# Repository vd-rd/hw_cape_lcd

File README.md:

# hw_cape_lcd
LCD module for embedded projects

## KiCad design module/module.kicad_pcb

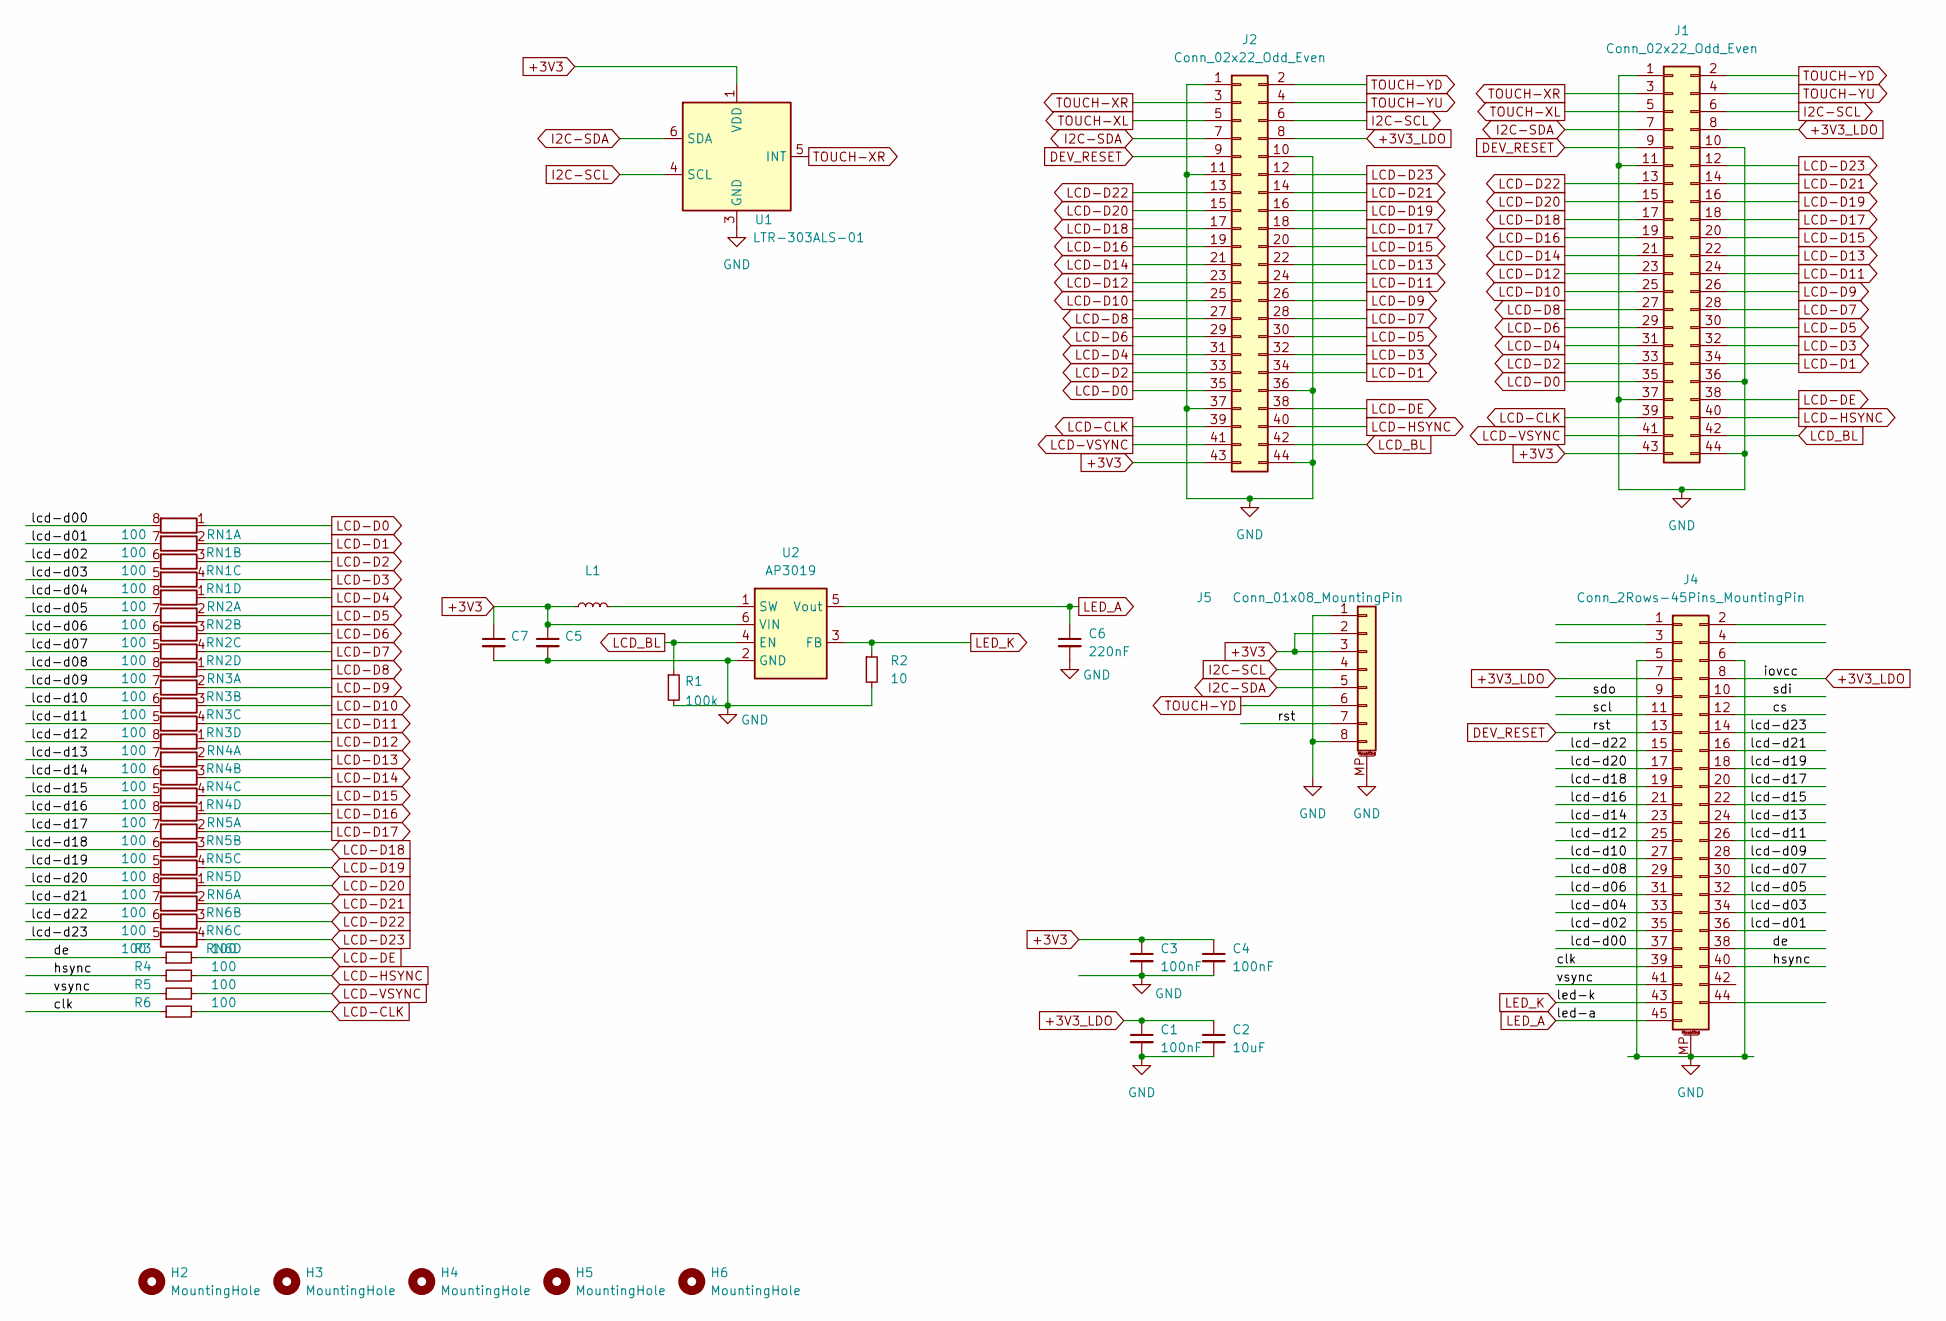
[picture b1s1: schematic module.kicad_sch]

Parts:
C1, C3, C4: 100nF; C_0402_1005Metric
C2: 10uF; C_0603_1608Metric
C5, C7: (no value)
C6: 220nF; C_0603_1608Metric
H2, H3, H4, H5, H6: MountingHole; MountingHole_2.7mm_M2.5_DIN965
J1, J2: Conn_02x22_Odd_Even; PinHeader_2x22_P1.27mm_Vertical_SMD
J4: Conn_2Rows-45Pins_MountingPin; Hirose_FH12-45S-0.5SH_1x45-1MP_P0.50mm_Horizontal
J5: Conn_01x08_MountingPin; Hirose_FH12-8S-0.5SH_1x08-1MP_P0.50mm_Horizontal
L1: (no value)
R1: 100k; R_0402_1005Metric
R2: 10; R_0805_2012Metric
R3, R4, R5, R6: 100; R_0603_1608Metric
RN1, RN2, RN3, RN4, RN5, RN6: 100; R_Array_Convex_4x0603
U1: LTR-303ALS-01; Lite-On_LTR-303ALS-01
U2: AP3019; SOT-23-6

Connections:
+3V3: C3.1, C4.1, C5.1, C7.1, J1.43, J2.43, J5.2, J5.3, L1.1, U1.1 (VDD), U2.6 (VIN)
+3V3_LDO: C1.1, C2.1, J1.8, J2.8, J4.7, J4.8
/clk: J4.39, R6.1
/cs: J4.12
/de: J4.38, R3.1
/hsync: J4.40, R4.1
/lcd-d00: J4.37, RN1.8 (R1.2)
/lcd-d01: J4.36, RN1.7 (R2.2)
/lcd-d02: J4.35, RN1.6 (R3.2)
/lcd-d03: J4.34, RN1.5 (R4.2)
/lcd-d04: J4.33, RN2.8 (R1.2)
/lcd-d05: J4.32, RN2.7 (R2.2)
/lcd-d06: J4.31, RN2.6 (R3.2)
/lcd-d07: J4.30, RN2.5 (R4.2)
/lcd-d08: J4.29, RN3.8 (R1.2)
/lcd-d09: J4.28, RN3.7 (R2.2)
/lcd-d10: J4.27, RN3.6 (R3.2)
/lcd-d11: J4.26, RN3.5 (R4.2)
/lcd-d12: J4.25, RN4.8 (R1.2)
/lcd-d13: J4.24, RN4.7 (R2.2)
/lcd-d14: J4.23, RN4.6 (R3.2)
/lcd-d15: J4.22, RN4.5 (R4.2)
/lcd-d16: J4.21, RN5.8 (R1.2)
/lcd-d17: J4.20, RN5.7 (R2.2)
/lcd-d18: J4.19, RN5.6 (R3.2)
/lcd-d19: J4.18, RN5.5 (R4.2)
/lcd-d20: J4.17, RN6.8 (R1.2)
/lcd-d21: J4.16, RN6.7 (R2.2)
/lcd-d22: J4.15, RN6.6 (R3.2)
/lcd-d23: J4.14, RN6.5 (R4.2)
/scl: J4.11
/sdi: J4.10
/sdo: J4.9
/vsync: J4.41, R5.1
DEV_RESET: J1.9, J2.9, J4.13, J5.7
GND: C1.2, C2.2, C3.2, C4.2, C5.2, C6.2, C7.2, J1.1, J1.10, J1.11, J1.36, J1.37, J1.44, J2.1, J2.10, J2.11, J2.36, J2.37, J2.44, J4.5, J4.6, J4.MP (MountPin), J5.1, J5.8, J5.MP (MountPin), R1.2, R2.2, U1.3 (GND), U2.2 (GND)
I2C-SCL: J1.6, J2.6, J5.4, U1.4 (SCL)
I2C-SDA: J1.7, J2.7, J5.5, U1.6 (SDA)
LCD-CLK: J1.39, J2.39, R6.2
LCD-D0: J1.35, J2.35, RN1.1 (R1.1)
LCD-D1: J1.34, J2.34, RN1.2 (R2.1)
LCD-D2: J1.33, J2.33, RN1.3 (R3.1)
LCD-D3: J1.32, J2.32, RN1.4 (R4.1)
LCD-D4: J1.31, J2.31, RN2.1 (R1.1)
LCD-D5: J1.30, J2.30, RN2.2 (R2.1)
LCD-D6: J1.29, J2.29, RN2.3 (R3.1)
LCD-D7: J1.28, J2.28, RN2.4 (R4.1)
LCD-D8: J1.27, J2.27, RN3.1 (R1.1)
LCD-D9: J1.26, J2.26, RN3.2 (R2.1)
LCD-D10: J1.25, J2.25, RN3.3 (R3.1)
LCD-D11: J1.24, J2.24, RN3.4 (R4.1)
LCD-D12: J1.23, J2.23, RN4.1 (R1.1)
LCD-D13: J1.22, J2.22, RN4.2 (R2.1)
LCD-D14: J1.21, J2.21, RN4.3 (R3.1)
LCD-D15: J1.20, J2.20, RN4.4 (R4.1)
LCD-D16: J1.19, J2.19, RN5.1 (R1.1)
LCD-D17: J1.18, J2.18, RN5.2 (R2.1)
LCD-D18: J1.17, J2.17, RN5.3 (R3.1)
LCD-D19: J1.16, J2.16, RN5.4 (R4.1)
LCD-D20: J1.15, J2.15, RN6.1 (R1.1)
LCD-D21: J1.14, J2.14, RN6.2 (R2.1)
LCD-D22: J1.13, J2.13, RN6.3 (R3.1)
LCD-D23: J1.12, J2.12, RN6.4 (R4.1)
LCD-DE: J1.38, J2.38, R3.2
LCD-HSYNC: J1.40, J2.40, R4.2
LCD-VSYNC: J1.41, J2.41, R5.2
LCD_BL: J1.42, J2.42, R1.1, U2.4 (EN)
LED_A: C6.1, J4.45, U2.5 (Vout)
LED_K: J4.43, R2.1, U2.3 (FB)
unnamed: L1.2, U2.1 (SW)
TOUCH-XL: J1.5, J2.5
TOUCH-XR: J1.3, J2.3, U1.5 (INT)
TOUCH-YD: J1.2, J2.2, J5.6
TOUCH-YU: J1.4, J2.4

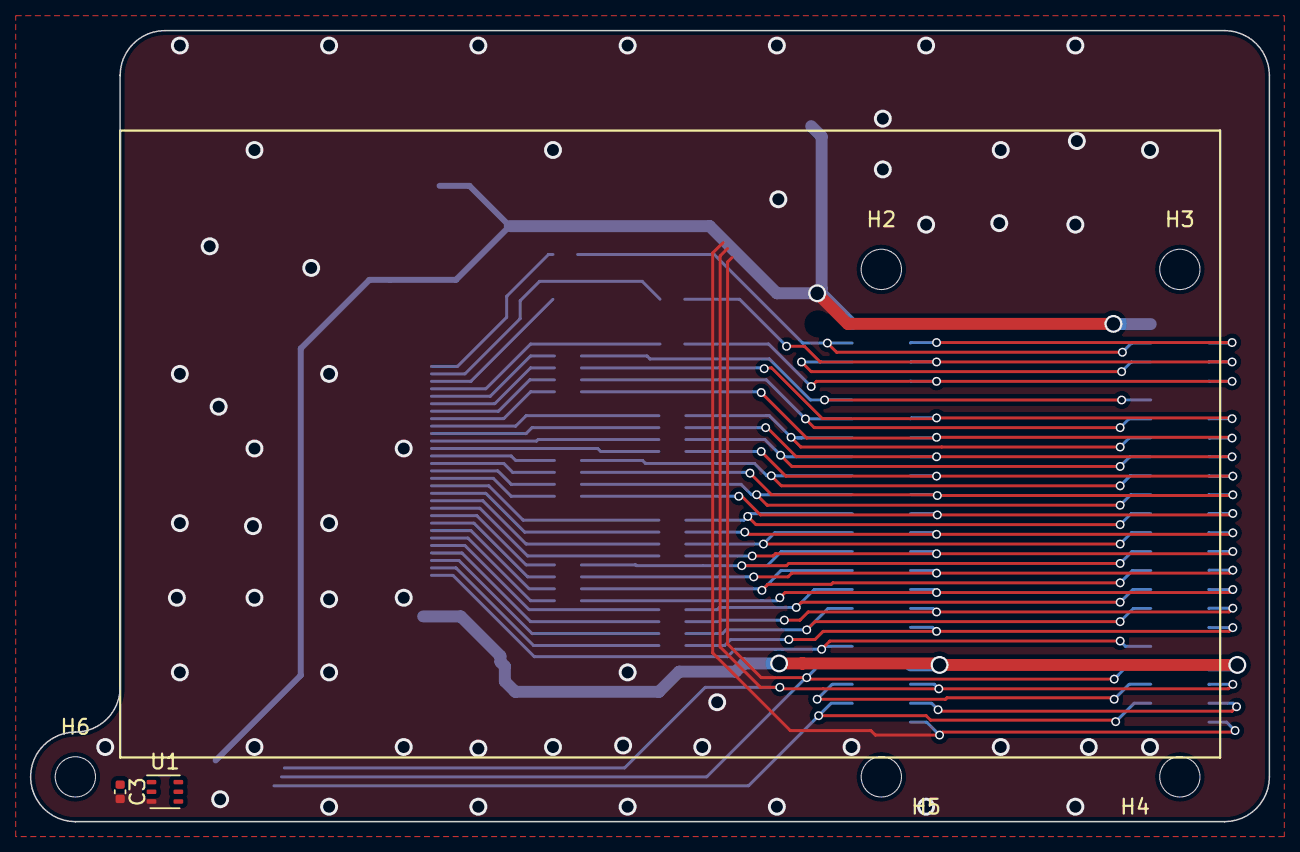
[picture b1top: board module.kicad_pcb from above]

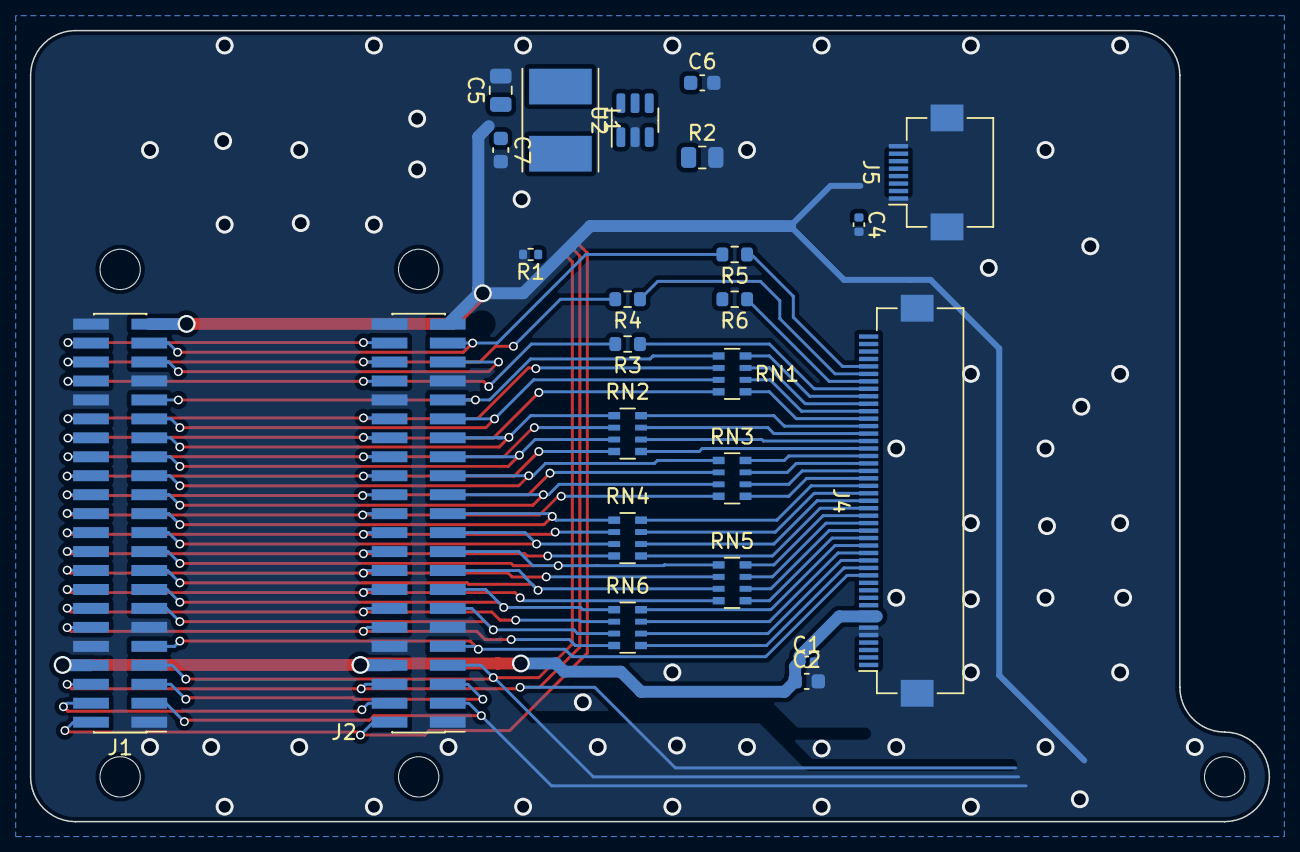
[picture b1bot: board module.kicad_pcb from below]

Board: 2 copper layers, 83.0 x 53.0 mm, 31 parts (24 on the bottom side), 70 nets.

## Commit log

2019-05-22 project: defined structure
2019-05-22 board: established floorplan and features
2022-04-17 switch to kicad
2022-04-17 add light sensor
2022-04-18 add routing for lcd connector
2022-04-25 defined shape for fascontek 3in lcd
2022-04-29 move from generic module to folders
